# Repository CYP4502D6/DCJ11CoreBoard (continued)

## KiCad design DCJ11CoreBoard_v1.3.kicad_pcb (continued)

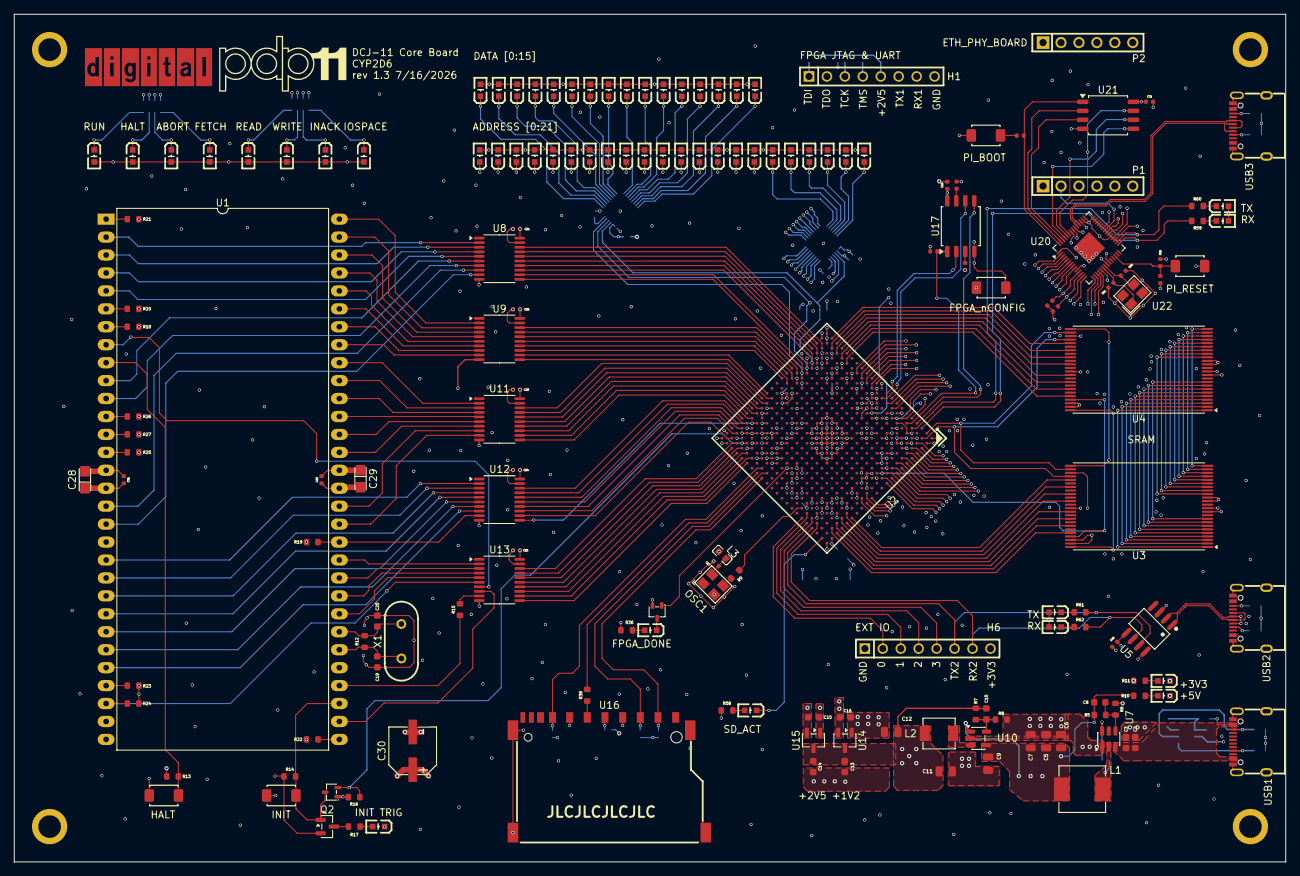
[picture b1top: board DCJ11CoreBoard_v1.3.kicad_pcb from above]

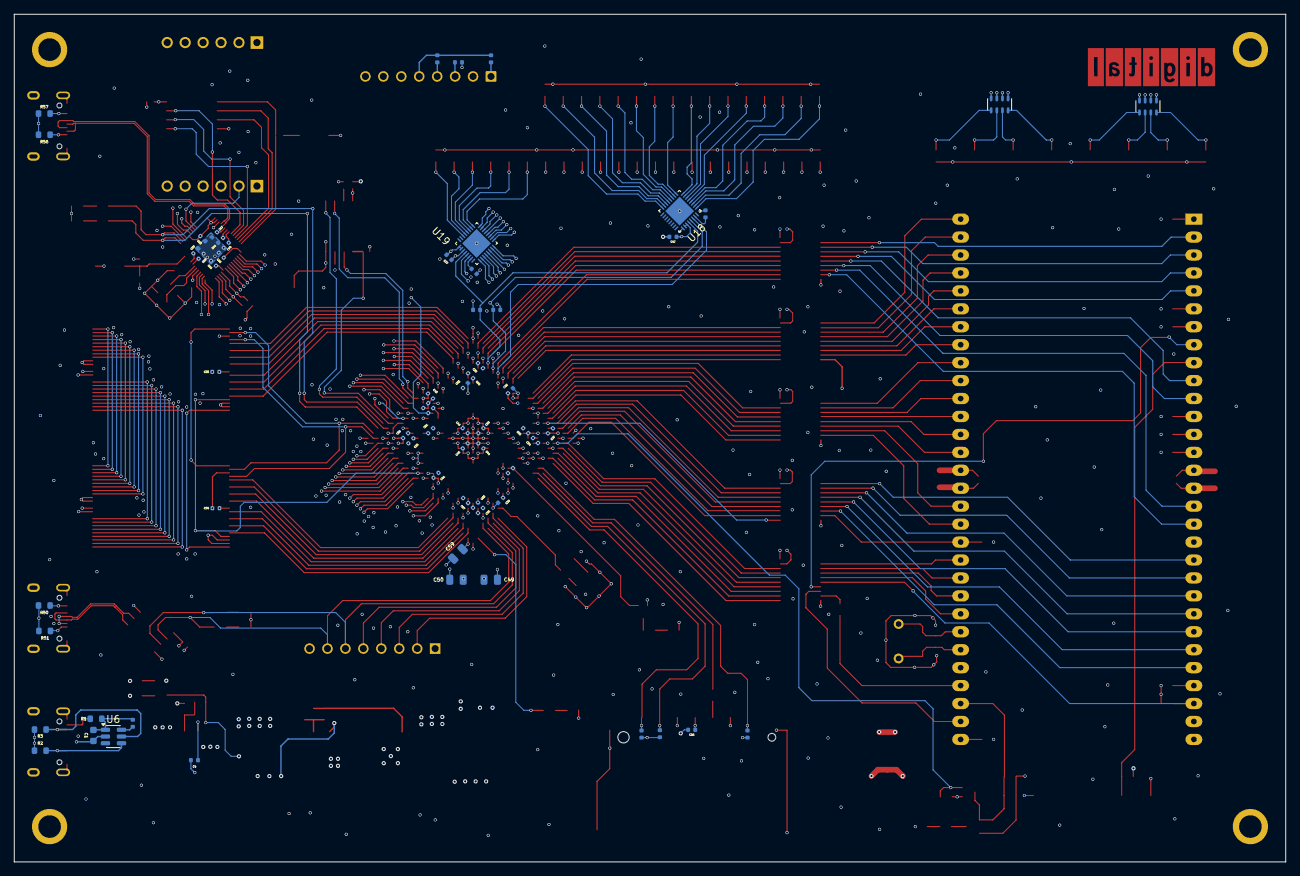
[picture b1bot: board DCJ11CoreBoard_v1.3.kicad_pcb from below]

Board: 6 copper layers, 180.0 x 120.0 mm, 232 parts (64 on the bottom side), 292 nets.

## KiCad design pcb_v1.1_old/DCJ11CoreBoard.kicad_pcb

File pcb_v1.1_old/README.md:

# PDP-11 Single-Board-Computer Replication Project

Temporary specification sheet for the DEC DCJ-11 and FPGA-based PDP-11 replication hardware. Using FPGA as a bus controller and emulating peripherals such as disk drives.

## Core Hardware (v1.0 - v1.1)
* **CPU:** DEC DCJ-11
* **FPGA:** Gowin GW1N-LV9LQ144
* **SRAM:** 2× CY62167EV30LL
* **Bus voltage conversion:** 5× SN74CB3T3245PWR

---

## Hardware Revisions

### v1.0 (Fabricated)

**Known Issues:**
* CH221K (USB PD): Missing series resistors on power lines.
* SD Slot: VCC and GND pins are inverted.
* CH347: Incompatible as a Gowin JTAG debugger.
* The absence of balanced copper on the top and bottom layers caused thermal expansion and contraction issues during SMT production.

### v1.1 (Unfabricated)
* Errata from v1.0 fixed in design files. Production bypassed.

### v1.2 (In Development)
* **Architecture Change:** Migrating to Altera Cyclone IV EP4CE15F23 and Raspberry Pi RP2040. Integrating original PDP-11 front panel status indicators.

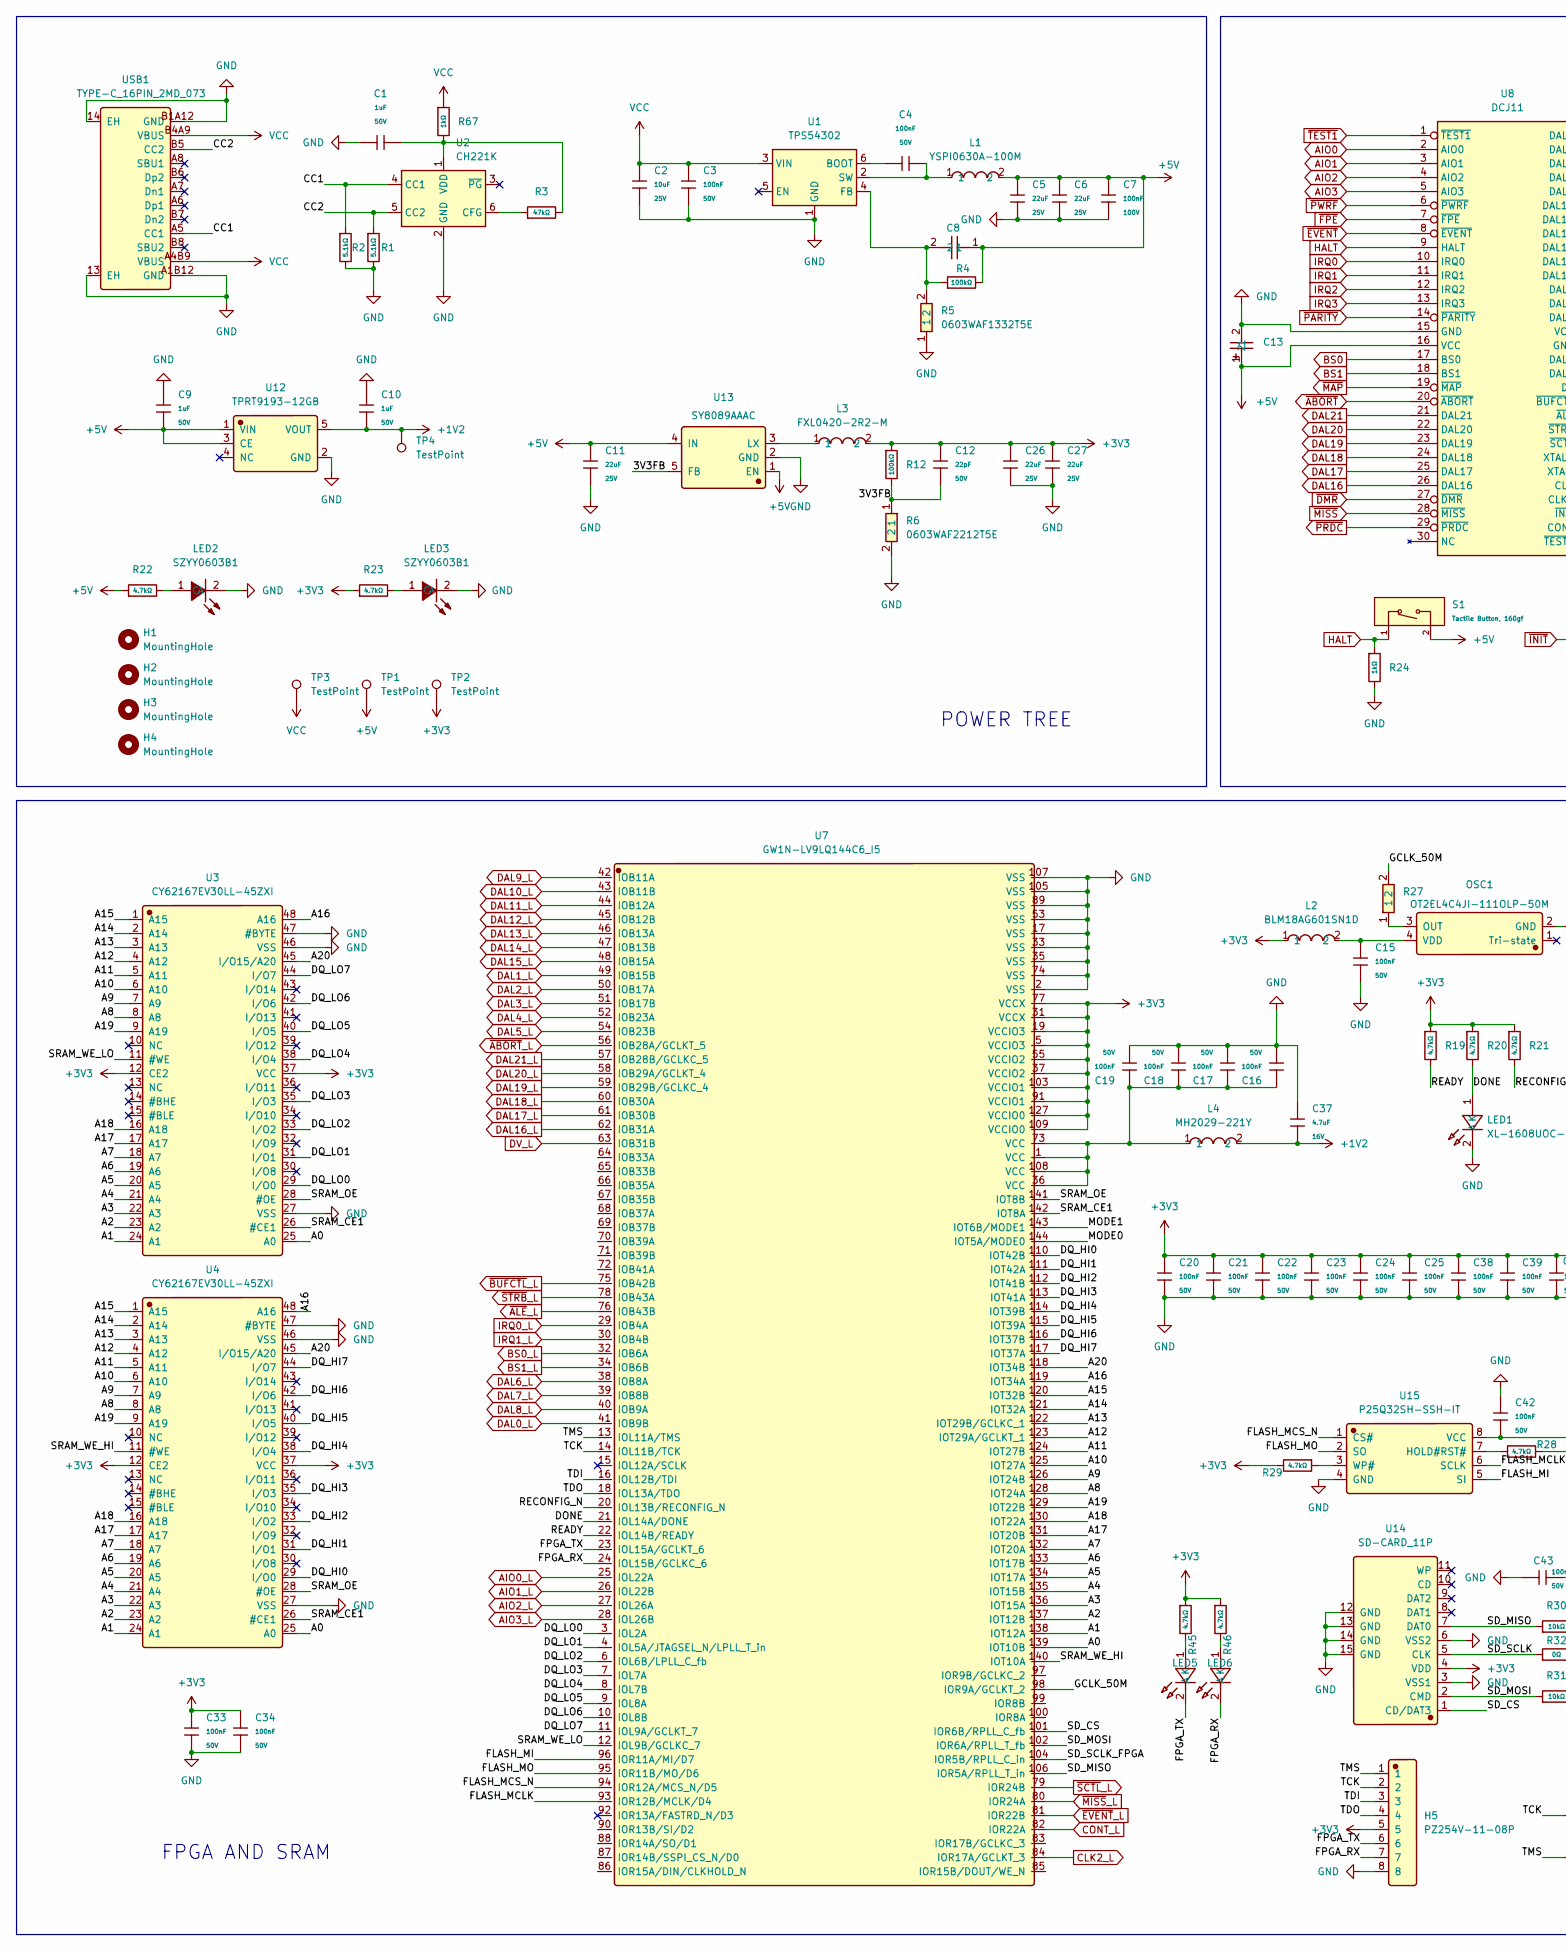
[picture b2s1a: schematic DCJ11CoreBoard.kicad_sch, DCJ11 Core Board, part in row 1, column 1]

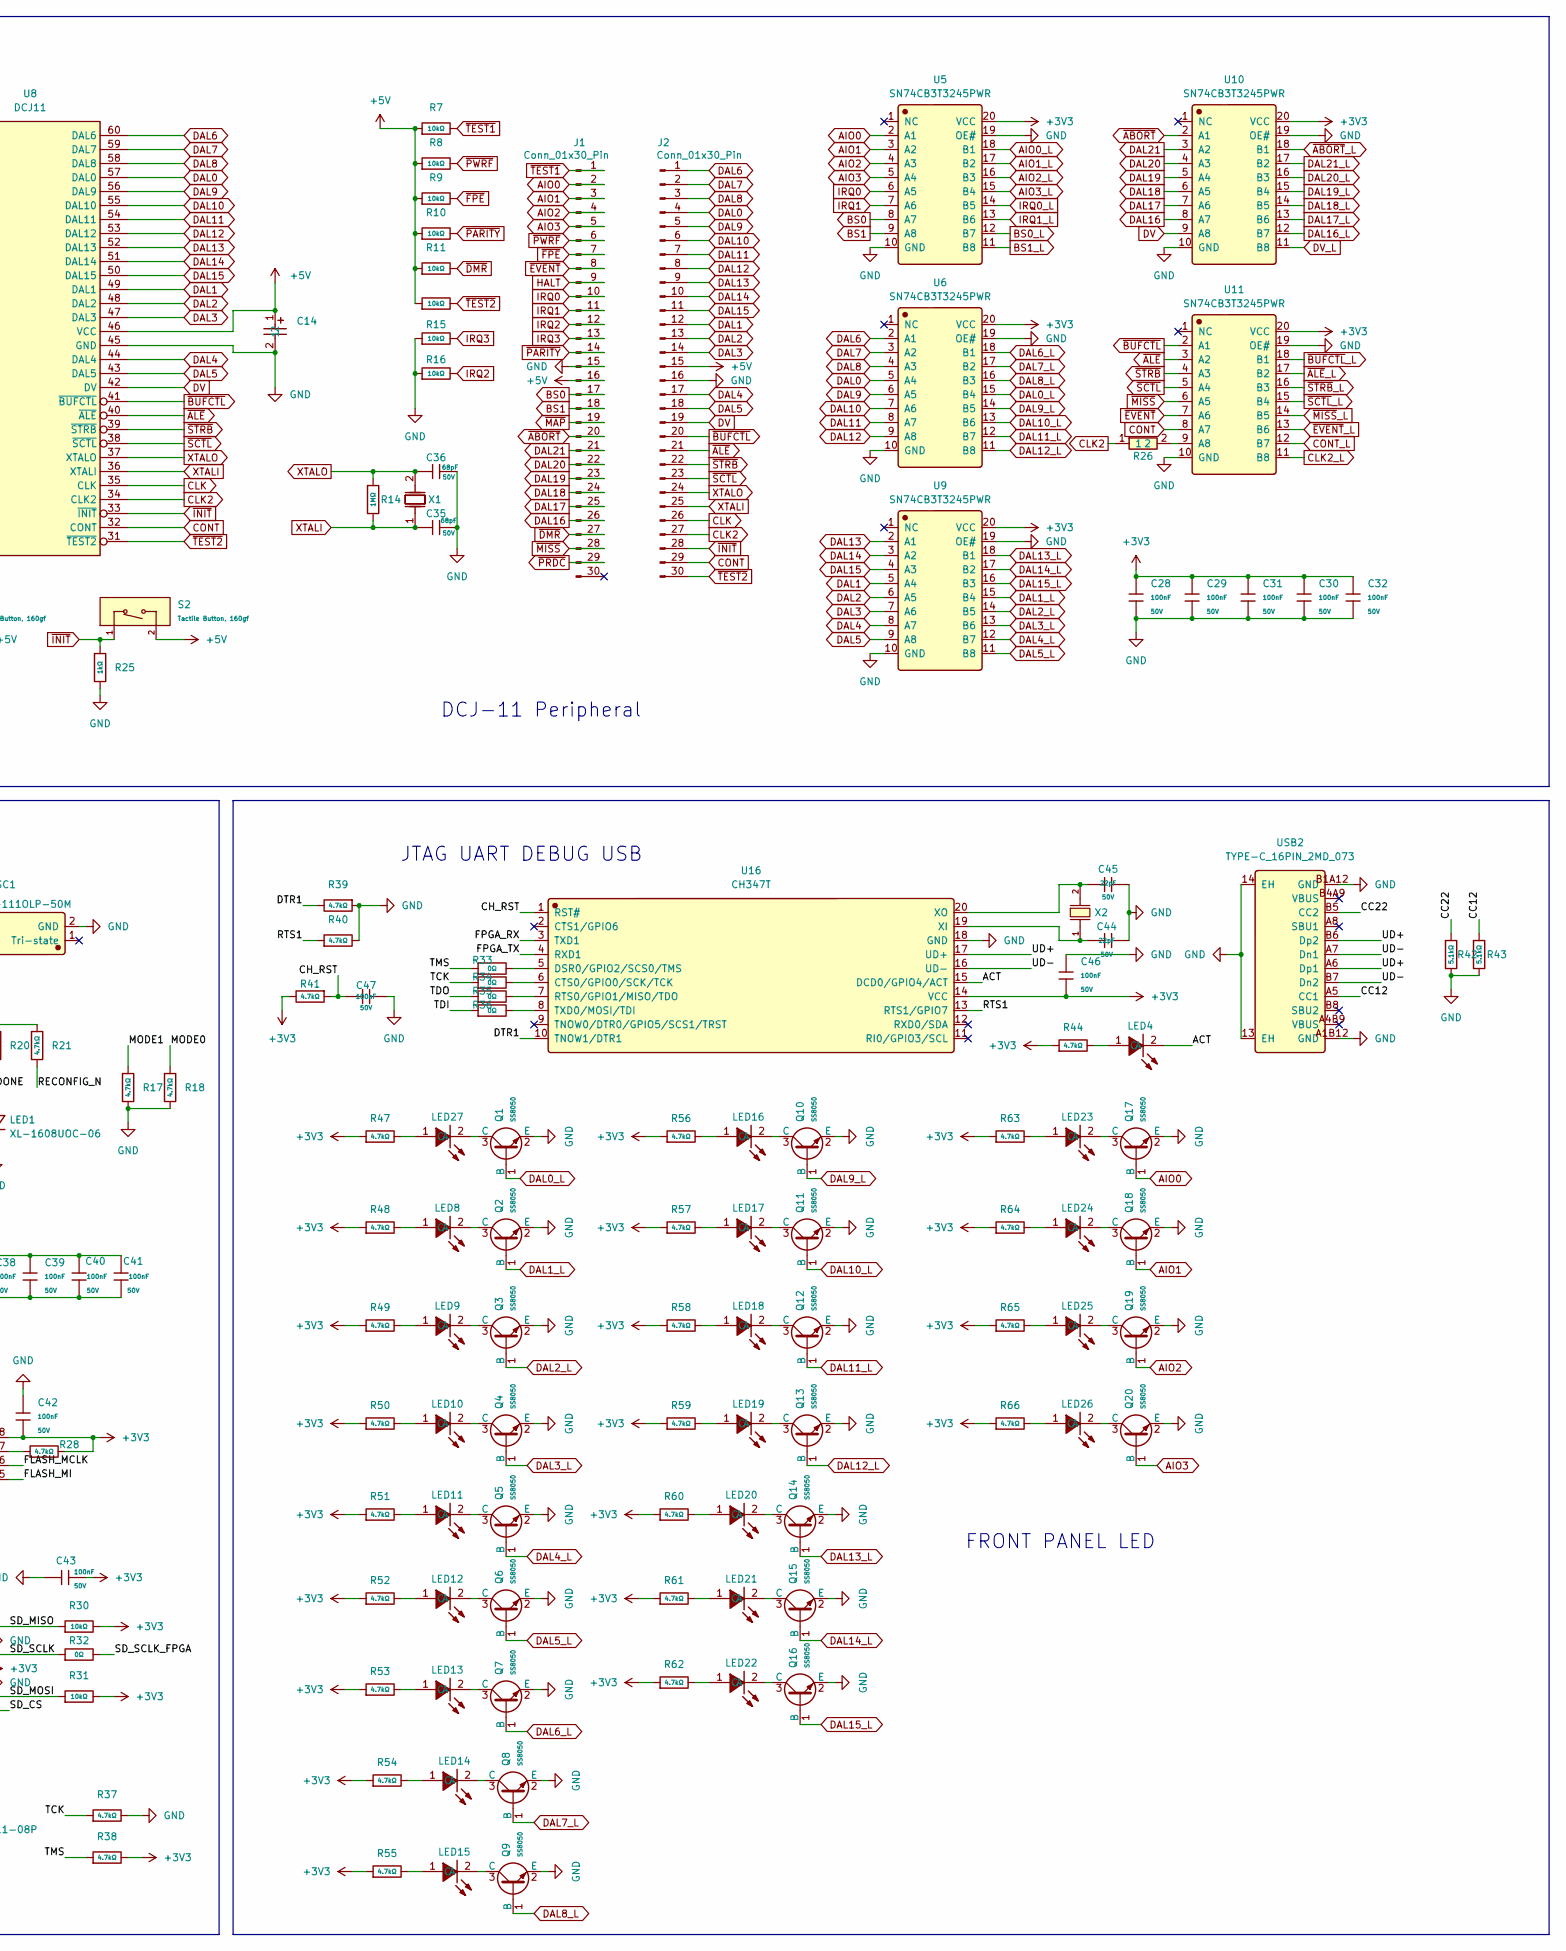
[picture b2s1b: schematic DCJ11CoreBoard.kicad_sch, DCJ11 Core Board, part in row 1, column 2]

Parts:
C1, C9, C10: 1uF; C_0603; Voltage Rated 50V; Tolerance ±10%; Part CL10A105KB8NNNC; LCSC C15849
C2: 10uF; C_0603; Voltage Rated 25V; Tolerance ±20%; Part CL10A106MA8NRNC; LCSC C96446
C3, C4, C15, C16, C17, C18, C19, C20, C21, C22, C23, C24, C25, C28, C29, C30, C31, C32, C33, C34, C38, C39, C40, C41, C42, C43, C46, C47: 100nF; C_0603; Voltage Rated 50V; Tolerance ±10%; Part CC0603KRX7R9BB104; LCSC C14663
C5, C6, C11, C26, C27: 22uF; C_0805; Voltage Rated 25V; Tolerance ±20%; Part CL21A226MAQNNNE; LCSC C45783
C7: 100nF; C_0805; Voltage Rated 100V; Tolerance ±10%; Part CL21B104KCFNNNE; LCSC C28233
C8: CC0603JRNPO9BN750; C_0603; Manufacturer Part CC0603JRNPO9BN750; LCSC C282074
C12, C44, C45: 22pF; C_0603; Voltage Rated 50V; Tolerance ±5%; Part CL10C220JB8NNNC; LCSC C1653
C13, C14: TAJA334K035RNJ; Manufacturer Part TAJA334K035RNJ; LCSC C8014
C35, C36: 68pF; C_0603; Voltage Rated 50V; Tolerance ±5%; Part CL10C680JB8NNNC; LCSC C28262
C37: 4.7uF; C_0603; Voltage Rated 16V; Tolerance ±10%; Part CL10A475KO8NNNC; LCSC C19666
H1, H2, H3, H4: MountingHole; MountingHole_2.5mm
H5: PZ254V-11-08P; Manufacturer Part PZ254V-11-08P; LCSC C492407
J1, J2: Conn_01x30_Pin; PinHeader_1x30_P2.54mm_Vertical
L1: YSPI0630A-100M; Manufacturer Part YSPI0630A-100M; LCSC C497871
L2: BLM18AG601SN1D; Manufacturer Part BLM18AG601SN1D; LCSC C19330
L3: FXL0420-2R2-M; Manufacturer Part FXL0420-2R2-M; LCSC C167206
L4: MH2029-221Y; Manufacturer Part MH2029-221Y; LCSC C840594
LED1, LED5, LED6: XL-1608UOC-06; Manufacturer Part XL-1608UOC-06; LCSC C965800
LED2, LED3, LED4, LED8, LED9, LED10, LED11, LED12, LED13, LED14, LED15, LED16, LED17, LED18, LED19, LED20, LED21, LED22, LED23, LED24, LED25, LED26, LED27: SZYY0603B1; Manufacturer Part SZYY0603B1; LCSC C19712531
OSC1: OT2EL4C4JI-111OLP-50M; Manufacturer Part OT2EL4C4JI-111OLP-50M; LCSC C5203552
Q1, Q2, Q3, Q4, Q5, Q6, Q7, Q8, Q9, Q10, Q11, Q12, Q13, Q14, Q15, Q16, Q17, Q18, Q19, Q20: SS8050; Q_SOT-23; Part SS8050; LCSC C431710
R1, R2, R42, R43: 5.1kΩ; R_0603; Overload Voltage (Max) 75V; Tolerance ±1%; Part 0603WAF5101T5E; LCSC C23186
R3: 47kΩ; R_0603; Overload Voltage (Max) 75V; Tolerance ±1%; Part 0603WAF4702T5E; LCSC C25819
R4, R12: 100kΩ; R_0603; Overload Voltage (Max) 75V; Tolerance ±1%; Part 0603WAF1003T5E; LCSC C25803
R5: 0603WAF1332T5E; R_0603; Manufacturer Part 0603WAF1332T5E; LCSC C25952
R6: 0603WAF2212T5E; R_0603; Manufacturer Part 0603WAF2212T5E; LCSC C25961
R7, R8, R9, R10, R11, R13, R15, R16, R30, R31: 10kΩ; R_0603; Overload Voltage (Max) 75V; Tolerance ±1%; Part 0603WAF1002T5E; LCSC C25804
R14: 1MΩ; R_0603; Overload Voltage (Max) 75V; Tolerance ±1%; Part 0603WAF1004T5E; LCSC C22935
R17, R18, R19, R20, R21, R22, R23, R28, R29, R37, R38, R39, R40, R41, R44, R45, R46, R47, R48, R49, R50, R51, R52, R53, R54, R55, R56, R57, R58, R59, R60, R61, R62, R63, R64, R65, R66: 4.7kΩ; R_0603; Overload Voltage (Max) 75V; Tolerance ±1%; Part 0603WAF4701T5E; LCSC C23162
R24, R25, R67: 1kΩ; R_0603; Overload Voltage (Max) 75V; Tolerance ±1%; Part 0603WAF1001T5E; LCSC C21190
R26, R27: 0603WAF220JT5E; R_0603; Manufacturer Part 0603WAF220JT5E; LCSC C23345
R32, R33, R34, R35, R36: 0Ω; R_0603; Overload Voltage (Max) 75V; Tolerance ±1%; Part 0603WAF0000T5E; LCSC C21189
S1, S2: Tactile Button, 160gf; SW_TS-1088-AR02016; Voltage Rating (Dc) 12V; Part TS-1088-AR02016; LCSC C720477
TP1, TP2, TP3, TP4: TestPoint; TestPoint_Pad_D1.0mm
U1: TPS54302; SOT-23-6
U2: CH221K; SOT-23-6
U3, U4: CY62167EV30LL-45ZXI; TSOP-I-48_18.4x12mm_P0.5mm; Manufacturer Part CY62167EV30LL-45ZXI; LCSC C115715
U5, U6, U9, U10, U11: SN74CB3T3245PWR; TSSOP-20_4.4x6.5mm_P0.65mm; Manufacturer Part SN74CB3T3245PWR; LCSC C15298
U7: GW1N-LV9LQ144C6_I5; Manufacturer Part GW1N-LV9LQ144C6/I5; LCSC C5799572
U8: DCJ11; DIP-60_W33.02mm_LongPads
U12: TPRT9193-12GB; Manufacturer Part TPRT9193-12GB; LCSC C7202982
U13: SY8089AAAC; SOT-23-5; Manufacturer Part SY8089AAAC; LCSC C78988
U14: SD-CARD_11P; Manufacturer Part SD-CARD 11P; LCSC C7529393
U15: P25Q32SH-SSH-IT; Manufacturer Part P25Q32SH-SSH-IT; LCSC C2833294
U16: CH347T; Manufacturer Part CH347T; LCSC C5122332
USB1, USB2: TYPE-C_16PIN_2MD_073; Manufacturer Part TYPE-C 16PIN 2MD(073); LCSC C2765186
X1: 9BC18000151060C3; Manufacturer Part 9BC18000151060C3; LCSC C2715887
X2: X50328MSB2GI; CRYSTAL-SMD_L5.0-W3.2; Frequency Tolerance ±10ppm; Part X50328MSB2GI; LCSC C115962

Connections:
+1V2: C10.2, C37.2, L4.2, TP4.1 (1_1), U12.5 (VOUT)
+3V3: C12.1, C20.1, C21.1, C22.1, C23.1, C24.1, C25.1, C26.1, C27.1, C28.1, C29.1, C30.1, C31.1, C32.1, C33.1, C34.1, C38.1, C39.1, C40.1, C41.1, C42.2, C43.1, C46.2, H5.5, L2.1, L3.2, R12.1, R19.1, R20.1, R21.1, R23.1, R28.2, R29.2, R30.2, R31.2, R38.2, R41.2, R44.1, R45.1, R46.1, R47.1, R48.1, R49.1, R50.1, R51.1, R52.1, R53.1, R54.1, R55.1, R56.1, R57.1, R58.1, R59.1, R60.1, R61.1, R62.1, R63.1, R64.1, R65.1, R66.1, TP2.1 (1_1), U3.12 (CE2), U3.37 (VCC), U4.12 (CE2), U4.37 (VCC), U5.20 (VCC), U6.20 (VCC), U7.5 (VCCIO3), U7.19 (VCCIO3), U7.31 (VCCX), U7.37 (VCCIO2), U7.55 (VCCIO2), U7.77 (VCCX), U7.91 (VCCIO1), U7.103 (VCCIO1), U7.109 (VCCIO0), U7.127 (VCCIO0), U9.20 (VCC), U10.20 (VCC), U11.20 (VCC), U14.4 (VDD), U15.8 (VCC), U16.14 (VCC)
+5V: C5.1, C6.1, C7.1, C8.1, C9.1, C11.1, C13.1, C14.1, J1.16, J2.15, L1.2, R4.2, R7.1, R8.1, R9.1, R10.1, R11.1, R13.1, R22.1, S1.2 (B), S2.2 (B), TP1.1 (1_1), U8.16 (VCC), U8.46 (VCC), U12.1 (VIN), U12.3 (CE), U13.1 (EN), U13.4 (IN)
/3V3FB: C12.2, R6.1, R12.2, U13.5 (FB)
/A0: U3.25 (A0), U4.25 (A0), U7.139 (IOT10B)
/A1: U3.24 (A1), U4.24 (A1), U7.138 (IOT12A)
/A2: U3.23 (A2), U4.23 (A2), U7.137 (IOT12B)
/A3: U3.22 (A3), U4.22 (A3), U7.136 (IOT15A)
/A4: U3.21 (A4), U4.21 (A4), U7.135 (IOT15B)
/A5: U3.20 (A5), U4.20 (A5), U7.134 (IOT17A)
/A6: U3.19 (A6), U4.19 (A6), U7.133 (IOT17B)
/A7: U3.18 (A7), U4.18 (A7), U7.132 (IOT20A)
/A8: U3.8 (A8), U4.8 (A8), U7.128 (IOT24A)
/A9: U3.7 (A9), U4.7 (A9), U7.126 (IOT24B)
/A10: U3.6 (A10), U4.6 (A10), U7.125 (IOT27A)
/A11: U3.5 (A11), U4.5 (A11), U7.124 (IOT27B)
/A12: U3.4 (A12), U4.4 (A12), U7.123 (IOT29A/GCLKT_1)
/A13: U3.3 (A13), U4.3 (A13), U7.122 (IOT29B/GCLKC_1)
/A14: U3.2 (A14), U4.2 (A14), U7.121 (IOT32A)
/A15: U3.1 (A15), U4.1 (A15), U7.120 (IOT32B)
/A16: U3.48 (A16), U4.48 (A16), U7.119 (IOT34A)
/A17: U3.17 (A17), U4.17 (A17), U7.131 (IOT20B)
/A18: U3.16 (A18), U4.16 (A18), U7.130 (IOT22A)
/A19: U3.9 (A19), U4.9 (A19), U7.129 (IOT22B)
/A20: U3.45 (I/O15/A20), U4.45 (I/O15/A20), U7.118 (IOT34B)
/ACT: LED4.2 (C), U16.15 (DCD0/GPIO4/ACT)
/CC1: R2.1, U2.4 (CC1), USB1.A5 (CC1)
/CC2: R1.1, U2.5 (CC2), USB1.B5 (CC2)
/CC12: R43.1, USB2.A5 (CC1)
/CC22: R42.1, USB2.B5 (CC2)
/CH_RST: C47.1, R41.1, U16.1 (RST#)
/DONE: LED1.1 (K), R20.2, U7.21 (IOL14A/DONE)
/DQ_HI0: U4.29 (I/O0), U7.110 (IOT42B)
/DQ_HI1: U4.31 (I/O1), U7.111 (IOT42A)
/DQ_HI2: U4.33 (I/O2), U7.112 (IOT41B)
/DQ_HI3: U4.35 (I/O3), U7.113 (IOT41A)
/DQ_HI4: U4.38 (I/O4), U7.114 (IOT39B)
/DQ_HI5: U4.40 (I/O5), U7.115 (IOT39A)
/DQ_HI6: U4.42 (I/O6), U7.116 (IOT37B)
/DQ_HI7: U4.44 (I/O7), U7.117 (IOT37A)
/DQ_LO0: U3.29 (I/O0), U7.3 (IOL2A)
/DQ_LO1: U3.31 (I/O1), U7.4 (IOL5A/JTAGSEL_N/LPLL_T_in)
/DQ_LO2: U3.33 (I/O2), U7.6 (IOL6B/LPLL_C_fb)
/DQ_LO3: U3.35 (I/O3), U7.7 (IOL7A)
/DQ_LO4: U3.38 (I/O4), U7.8 (IOL7B)
/DQ_LO5: U3.40 (I/O5), U7.9 (IOL8A)
/DQ_LO6: U3.42 (I/O6), U7.10 (IOL8B)
/DQ_LO7: U3.44 (I/O7), U7.11 (IOL9A/GCLKT_7)
/DTR1: R39.2, U16.10 (TNOW1/DTR1)
/FLASH_MCLK: U7.93 (IOR12B/MCLK/D4), U15.6 (SCLK)
/FLASH_MCS_N: U7.94 (IOR12A/MCS_N/D5), U15.1 (CS#)
/FLASH_MI: U7.96 (IOR11A/MI/D7), U15.5 (SI)
/FLASH_MO: U7.95 (IOR11B/MO/D6), U15.2 (SO)
/FPGA_RX: H5.7, LED6.2 (A), U7.24 (IOL15B/GCLKC_6), U16.3 (TXD1)
/FPGA_TX: H5.6, LED5.2 (A), U7.23 (IOL15A/GCLKT_6), U16.4 (RXD1)
/GCLK_50M: R27.2, U7.98 (IOR9A/GCLKT_2)
/MODE0: R18.1, U7.144 (IOT5A/MODE0)
/MODE1: R17.1, U7.143 (IOT6B/MODE1)
/READY: R19.2, U7.22 (IOL14B/READY)
/RECONFIG_N: R21.2, U7.20 (IOL13B/RECONFIG_N)
/RTS1: R40.1, U16.13 (RTS1/GPIO7)
/SD_CS: U7.101 (IOR6B/RPLL_C_fb), U14.1 (CD/DAT3)
/SD_MISO: R30.1, U7.106 (IOR5A/RPLL_T_in), U14.7 (DAT0)
/SD_MOSI: R31.1, U7.102 (IOR6A/RPLL_T_fb), U14.2 (CMD)
/SD_SCLK: R32.1, U14.5 (CLK)
/SD_SCLK_FPGA: R32.2, U7.104 (IOR5B/RPLL_C_in)
/SRAM_CE1: U3.26 (#CE1), U4.26 (#CE1), U7.142 (IOT8A)
/SRAM_OE: U3.28 (#OE), U4.28 (#OE), U7.141 (IOT8B)
/SRAM_WE_HI: U4.11 (#WE), U7.140 (IOT10A)
/SRAM_WE_LO: U3.11 (#WE), U7.12 (IOL9B/GCLKC_7)
/TCK: H5.2, R34.1, R37.1, U7.14 (IOL11B/TCK)
/TDI: H5.3, R36.1, U7.16 (IOL12B/TDI)
/TDO: H5.4, R35.1, U7.18 (IOL13A/TDO)
/TMS: H5.1, R33.1, R38.1, U7.13 (IOL11A/TMS)
/UD+: U16.17 (UD+), USB2.A6 (Dp1), USB2.B6 (Dp2)
/UD-: U16.16 (UD-), USB2.A7 (Dn1), USB2.B7 (Dn2)
AIO0: J1.2, Q17.1 (B), U5.2 (A1), U8.2 (AIO0)
AIO0_L: U5.18 (B1), U7.25 (IOL22A)
AIO1: J1.3, Q18.1 (B), U5.3 (A2), U8.3 (AIO1)
AIO1_L: U5.17 (B2), U7.26 (IOL22B)
AIO2: J1.4, Q19.1 (B), U5.4 (A3), U8.4 (AIO2)
AIO2_L: U5.16 (B3), U7.27 (IOL26A)
AIO3: J1.5, Q20.1 (B), U5.5 (A4), U8.5 (AIO3)
AIO3_L: U5.15 (B4), U7.28 (IOL26B)
BS0: J1.17, U5.8 (A7), U8.17 (BS0)
BS0_L: U5.12 (B7), U7.32 (IOB6A)
BS1: J1.18, U5.9 (A8), U8.18 (BS1)
BS1_L: U5.11 (B8), U7.34 (IOB6B)
CLK: J2.26, U8.35 (CLK)
CLK2: J2.27, R26.1, U8.34 (CLK2)
CLK2_L: U7.84 (IOR17A/GCLKT_3), U11.11 (B8)
CONT: J2.29, U8.32 (CONT), U11.8 (A7)
CONT_L: U7.82 (IOR22A), U11.12 (B7)
DAL0: J2.4, U6.5 (A4), U8.57 (DAL0)
DAL0_L: Q1.1 (B), U6.15 (B4), U7.41 (IOB9B)
DAL1: J2.12, U8.49 (DAL1), U9.5 (A4)
DAL1_L: Q2.1 (B), U7.49 (IOB15B), U9.15 (B4)
DAL2: J2.13, U8.48 (DAL2), U9.6 (A5)
DAL2_L: Q3.1 (B), U7.50 (IOB17A), U9.14 (B5)
DAL3: J2.14, U8.47 (DAL3), U9.7 (A6)
DAL3_L: Q4.1 (B), U7.51 (IOB17B), U9.13 (B6)
DAL4: J2.17, U8.44 (DAL4), U9.8 (A7)
DAL4_L: Q5.1 (B), U7.52 (IOB23A), U9.12 (B7)
DAL5: J2.18, U8.43 (DAL5), U9.9 (A8)
DAL5_L: Q6.1 (B), U7.54 (IOB23B), U9.11 (B8)
DAL6: J2.1, U6.2 (A1), U8.60 (DAL6)
DAL6_L: Q7.1 (B), U6.18 (B1), U7.38 (IOB8A)
DAL7: J2.2, U6.3 (A2), U8.59 (DAL7)
DAL7_L: Q8.1 (B), U6.17 (B2), U7.39 (IOB8B)
DAL8: J2.3, U6.4 (A3), U8.58 (DAL8)
DAL8_L: Q9.1 (B), U6.16 (B3), U7.40 (IOB9A)
DAL9: J2.5, U6.6 (A5), U8.56 (DAL9)
DAL9_L: Q10.1 (B), U6.14 (B5), U7.42 (IOB11A)
DAL10: J2.6, U6.7 (A6), U8.55 (DAL10)
DAL10_L: Q11.1 (B), U6.13 (B6), U7.43 (IOB11B)
DAL11: J2.7, U6.8 (A7), U8.54 (DAL11)
DAL11_L: Q12.1 (B), U6.12 (B7), U7.44 (IOB12A)
DAL12: J2.8, U6.9 (A8), U8.53 (DAL12)
DAL12_L: Q13.1 (B), U6.11 (B8), U7.45 (IOB12B)
DAL13: J2.9, U8.52 (DAL13), U9.2 (A1)
DAL13_L: Q14.1 (B), U7.46 (IOB13A), U9.18 (B1)
DAL14: J2.10, U8.51 (DAL14), U9.3 (A2)
DAL14_L: Q15.1 (B), U7.47 (IOB13B), U9.17 (B2)
DAL15: J2.11, U8.50 (DAL15), U9.4 (A3)
DAL15_L: Q16.1 (B), U7.48 (IOB15A), U9.16 (B3)
DAL16: J1.26, U8.26 (DAL16), U10.8 (A7)
DAL16_L: U7.62 (IOB31A), U10.12 (B7)
DAL17: J1.25, U8.25 (DAL17), U10.7 (A6)
DAL17_L: U7.61 (IOB30B), U10.13 (B6)
DAL18: J1.24, U8.24 (DAL18), U10.6 (A5)
DAL18_L: U7.60 (IOB30A), U10.14 (B5)
DAL19: J1.23, U8.23 (DAL19), U10.5 (A4)
DAL19_L: U7.59 (IOB29B/GCLKC_4), U10.15 (B4)
DAL20: J1.22, U8.22 (DAL20), U10.4 (A3)
DAL20_L: U7.58 (IOB29A/GCLKT_4), U10.16 (B3)
DAL21: J1.21, U8.21 (DAL21), U10.3 (A2)
DAL21_L: U7.57 (IOB28B/GCLKC_5), U10.17 (B2)
DV: J2.19, U8.42 (DV), U10.9 (A8)
DV_L: U7.63 (IOB31B), U10.11 (B8)
GND: C1.1, C2.2, C3.2, C5.2, C6.2, C7.2, C9.2, C10.1, C11.2, C13.2, C14.2, C15.2, C16.2, C17.2, C18.2, C19.2, C20.2, C21.2, C22.2, C23.2, C24.2, C25.2, C26.2, C27.2, C28.2, C29.2, C30.2, C31.2, C32.2, C33.2, C34.2, C35.1, C36.2, C37.1, C38.2, C39.2, C40.2, C41.2, C42.1, C43.2, C44.2, C45.2, C46.1, C47.2, H5.8, J1.15, J2.16, LED1.2 (A), LED2.2 (C), LED3.2 (C), OSC1.2 (GND), Q1.2 (E), Q2.2 (E), Q3.2 (E), Q4.2 (E), Q5.2 (E), Q6.2 (E), Q7.2 (E), Q8.2 (E), Q9.2 (E), Q10.2 (E), Q11.2 (E), Q12.2 (E), Q13.2 (E), Q14.2 (E), Q15.2 (E), Q16.2 (E), Q17.2 (E), Q18.2 (E), Q19.2 (E), Q20.2 (E), R1.2, R2.2, R5.1, R6.2, R15.1, R16.1, R17.2, R18.2, R24.2, R25.2, R37.2, R39.1, R40.2, R42.2, R43.2, U1.1 (GND), U2.2 (GND), U3.27 (VSS), U3.46 (VSS), U3.47 (#BYTE), U4.27 (VSS), U4.46 (VSS), U4.47 (#BYTE), U5.10 (GND), U5.19 (OE#), U6.10 (GND), U6.19 (OE#), U7.2 (VSS), U7.17 (VSS), U7.33 (VSS), U7.35 (VSS), U7.53 (VSS), U7.74 (VSS), U7.89 (VSS), U7.105 (VSS), U7.107 (VSS), U8.15 (GND), U8.45 (GND), U9.10 (GND), U9.19 (OE#), U10.10 (GND), U10.19 (OE#), U11.10 (GND), U11.19 (OE#), U12.2 (GND), U13.2 (GND), U14.3 (VSS1), U14.6 (VSS2), U14.12 (GND), U14.13 (GND), U14.14 (GND), U14.15 (GND), U15.4 (GND), U16.18 (GND), USB1.13 (EH), USB1.14 (EH), USB1.A1B12 (GND), USB1.B1A12 (GND), USB2.13 (EH), USB2.14 (EH), USB2.A1B12 (GND), USB2.B1A12 (GND)
HALT: J1.9, R24.1, S1.1 (A), U8.9 (HALT)
IRQ0: J1.10, U5.6 (A5), U8.10 (IRQ0)
IRQ0_L: U5.14 (B5), U7.29 (IOB4A)
IRQ1: J1.11, U5.7 (A6), U8.11 (IRQ1)
IRQ1_L: U5.13 (B6), U7.30 (IOB4B)
IRQ2: J1.12, R16.2, U8.12 (IRQ2)
IRQ3: J1.13, R15.2, U8.13 (IRQ3)
unnamed: C16.1, C17.1, C18.1, C19.1, L4.1, U7.1 (VCC), U7.36 (VCC), U7.73 (VCC), U7.108 (VCC)
unnamed: LED2.1 (A), R22.2
unnamed: LED3.1 (A), R23.2
unnamed: LED4.1 (A), R44.2
unnamed: LED5.1 (K), R45.2
unnamed: LED6.1 (K), R46.2
unnamed: LED8.1 (A), R48.2
unnamed: LED8.2 (C), Q2.3 (C)
unnamed: LED9.1 (A), R49.2
unnamed: LED9.2 (C), Q3.3 (C)
unnamed: LED10.1 (A), R50.2
unnamed: LED10.2 (C), Q4.3 (C)
unnamed: LED11.1 (A), R51.2
unnamed: LED11.2 (C), Q5.3 (C)
unnamed: LED12.1 (A), R52.2
unnamed: LED12.2 (C), Q6.3 (C)
unnamed: LED13.1 (A), R53.2
unnamed: LED13.2 (C), Q7.3 (C)
unnamed: LED14.1 (A), R54.2
unnamed: LED14.2 (C), Q8.3 (C)
unnamed: LED15.1 (A), R55.2
unnamed: LED15.2 (C), Q9.3 (C)
unnamed: LED16.1 (A), R56.2
unnamed: LED16.2 (C), Q10.3 (C)
unnamed: LED17.1 (A), R57.2
unnamed: LED17.2 (C), Q11.3 (C)
unnamed: LED18.1 (A), R58.2
unnamed: LED18.2 (C), Q12.3 (C)
unnamed: LED19.1 (A), R59.2
unnamed: LED19.2 (C), Q13.3 (C)
unnamed: LED20.1 (A), R60.2
unnamed: LED20.2 (C), Q14.3 (C)
unnamed: LED21.1 (A), R61.2
unnamed: LED21.2 (C), Q15.3 (C)
unnamed: LED22.1 (A), R62.2
unnamed: LED22.2 (C), Q16.3 (C)
unnamed: LED23.1 (A), R63.2
unnamed: LED23.2 (C), Q17.3 (C)
unnamed: LED24.1 (A), R64.2
unnamed: LED24.2 (C), Q18.3 (C)
unnamed: LED25.1 (A), R65.2
unnamed: LED25.2 (C), Q19.3 (C)
unnamed: LED26.1 (A), R66.2
unnamed: LED26.2 (C), Q20.3 (C)
unnamed: LED27.1 (A), R47.2
unnamed: LED27.2 (C), Q1.3 (C)
unnamed: OSC1.3 (OUT), R27.1
unnamed: C15.1, L2.2, OSC1.4 (VDD)
unnamed: C4.1, U1.6 (BOOT)
unnamed: C8.2, R4.1, R5.2, U1.4 (FB)
unnamed: C4.2, L1.1, U1.2 (SW)
unnamed: R3.1, U2.6 (CFG)
unnamed: C1.2, R3.2, R67.2, U2.1 (VDD)
unnamed: R26.2, U11.9 (A8)
unnamed: L3.1, U13.3 (LX)
unnamed: R28.1, U15.7 (HOLD#RST#)
unnamed: R29.1, U15.3 (WP#)
unnamed: R34.2, U16.6 (CTS0/GPIO0/SCK/TCK)
unnamed: R33.2, U16.5 (DSR0/GPIO2/SCS0/TMS)
unnamed: R35.2, U16.7 (RTS0/GPIO1/MISO/TDO)
unnamed: R36.2, U16.8 (TXD0/MOSI/TDI)
unnamed: C44.1, U16.19 (XI), X2.1
unnamed: C45.1, U16.20 (XO), X2.2
VCC: C2.1, C3.1, R67.1, TP3.1 (1_1), U1.3 (VIN), USB1.A4B9 (VBUS), USB1.B4A9 (VBUS)
XTALI: C35.2, J2.25, R14.2, U8.36 (XTALI), X1.1 (OSC1)
XTALO: C36.1, J2.24, R14.1, U8.37 (XTALO), X1.2 (OSC2)
~ABORT: J1.20, U8.20 (~ABORT), U10.2 (A1)
~ABORT_L: U7.56 (IOB28A/GCLKT_5), U10.18 (B1)
~ALE: J2.21, U8.40 (~ALE), U11.3 (A2)
~ALE_L: U7.76 (IOB43B), U11.17 (B2)
~BUFCTL: J2.20, U8.41 (~BUFCTL), U11.2 (A1)
~BUFCTL_L: U7.75 (IOB42B), U11.18 (B1)
~DMR: J1.27, R11.2, U8.27 (~DMR)
~EVENT: J1.8, U8.8 (~EVENT), U11.7 (A6)
~EVENT_L: U7.81 (IOR22B), U11.13 (B6)
~FPE: J1.7, R9.2, U8.7 (~FPE)
~INIT: J2.28, R25.1, S2.1 (A), U8.33 (~INIT)
~MAP: J1.19, U8.19 (~MAP)
~MISS: J1.28, U8.28 (~MISS), U11.6 (A5)
~MISS_L: U7.80 (IOR24A), U11.14 (B5)
~PARITY: J1.14, R10.2, U8.14 (~PARITY)
~PRDC: J1.29, U8.29 (~PRDC)
~PWRF: J1.6, R8.2, U8.6 (~PWRF)
~SCTL: J2.23, U8.38 (~SCTL), U11.5 (A4)
~SCTL_L: U7.79 (IOR24B), U11.15 (B4)
~STRB: J2.22, U8.39 (~STRB), U11.4 (A3)
~STRB_L: U7.78 (IOB43A), U11.16 (B3)
~TEST1: J1.1, R7.2, U8.1 (~TEST1)
~TEST2: J2.30, R13.2, U8.31 (~TEST2)

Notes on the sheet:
FRONT PANEL LED
DCJ-11 Peripheral
POWER TREE
JTAG UART DEBUG USB
FPGA AND SRAM

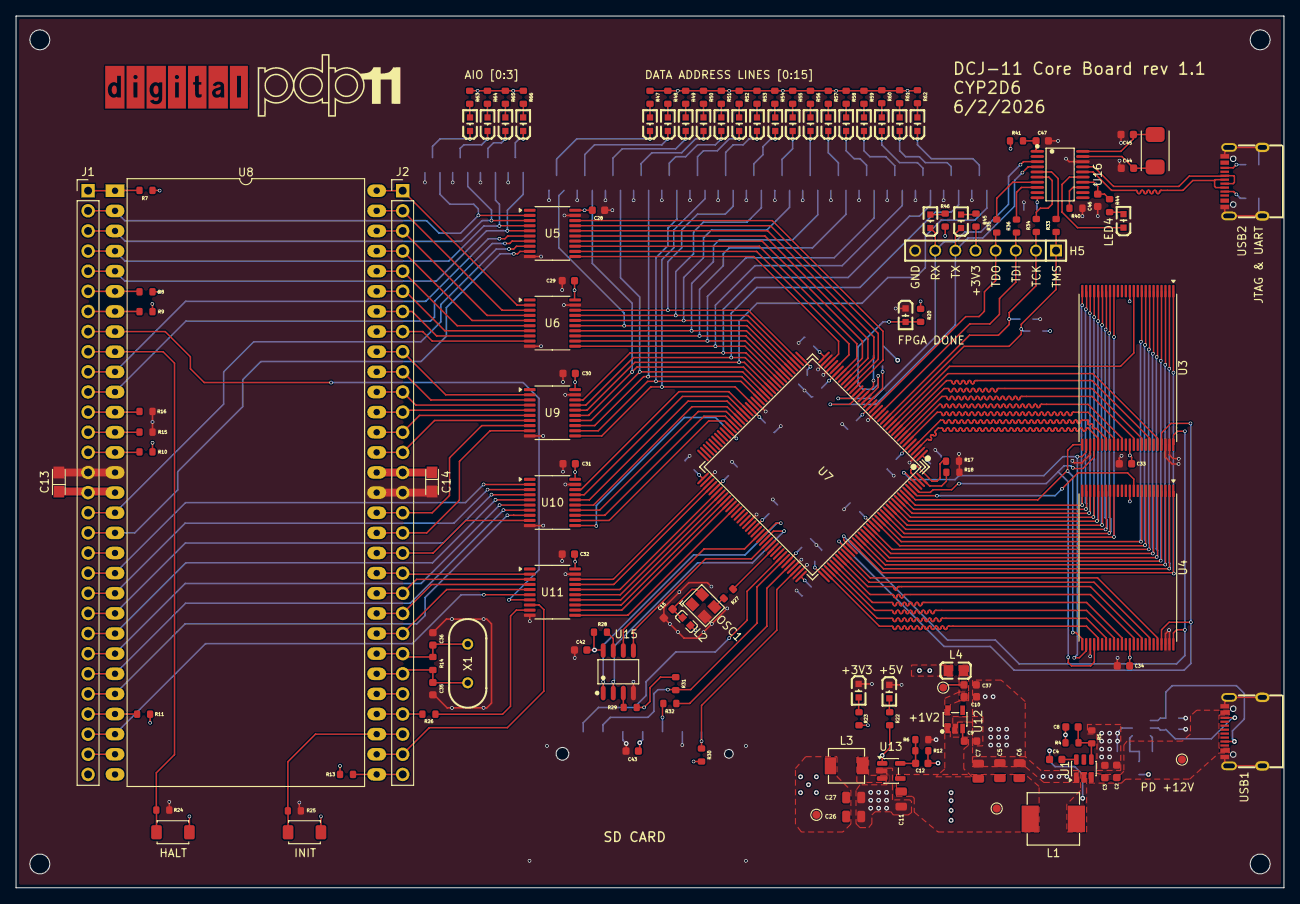
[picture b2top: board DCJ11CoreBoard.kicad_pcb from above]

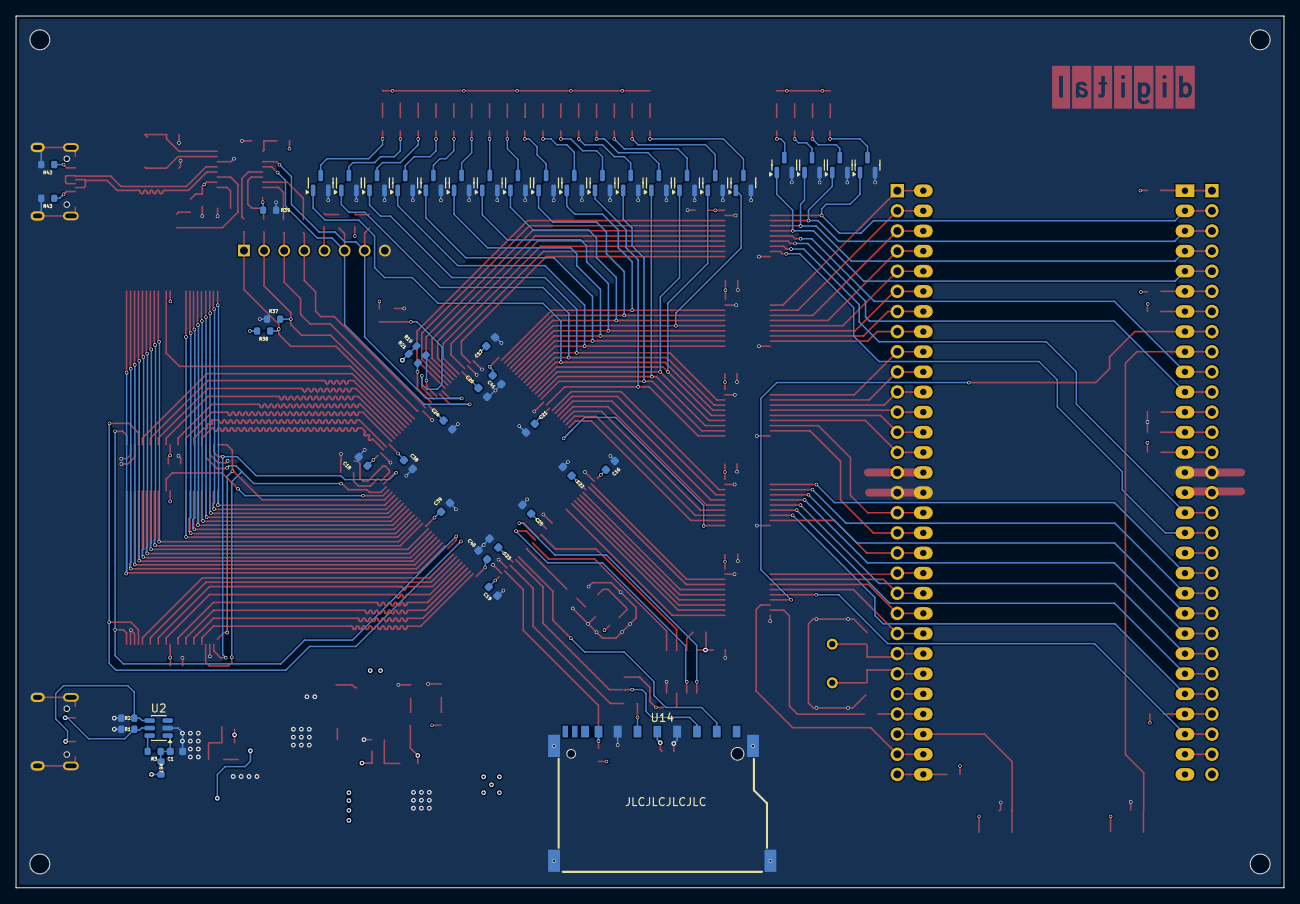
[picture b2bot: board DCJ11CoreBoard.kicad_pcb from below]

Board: 4 copper layers, 160.0 x 110.0 mm, 198 parts (48 on the bottom side), 236 nets.

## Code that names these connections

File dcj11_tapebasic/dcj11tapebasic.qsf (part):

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set_location_assignment PIN_R21 -to sd_spi_miso
set_location_assignment PIN_P22 -to sd_spi_cs_n

set_location_assignment PIN_R19 -to led_run
set_location_assignment PIN_R18 -to led_halt
set_location_assignment PIN_R16 -to led_fetch
set_location_assignment PIN_R15 -to led_read
set_location_assignment PIN_R14 -to led_write
set_location_assignment PIN_R13 -to led_inack
set_location_assignment PIN_R12 -to led_io_space
set_location_assignment PIN_R17 -to led_err
set_location_assignment PIN_Y7 -to led_i2c_scl
set_location_assignment PIN_Y6 -to led_i2c_sda
set_location_assignment PIN_Y4 -to led_addr_en
set_location_assignment PIN_Y8 -to led_data_en

set_global_assignment -name ENABLE_OCT_DONE OFF
set_global_assignment -name USE_CONFIGURATION_DEVICE OFF
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
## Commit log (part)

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2026-05-23 first version PCB implementation
2026-06-24 add status led and aw21024 front panel led controller test hdl
2026-06-24 add uart test hdl
2026-06-24 modify the value of PD negotiation chip's cfg resistor
2026-06-24 add SRAM test hdl
2026-06-26 add README for hardware rev 1.2 and initial system bring-up project for DCJ-11 CPU
2026-06-26 remove build artifacts and intermediate compilation products
2026-06-29 add paper tape basic for dcj-11 project
